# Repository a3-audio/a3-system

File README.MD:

# Ambijocky

Goal for this project is a Hardware Controller which enables everybody, who can use a dj-mixer, to perform
LIVE on a 3d-Audio-sphere (Ambisonic). You should consider it as loopmachine for panning motions. It
includes audiostream analysis to create a reliable live beatclock, wich let the user control step motions
out of bars, steps and bpm).

It consists of three elements:

- The Server which runs the audio and osc-routing-engine (live io-processing)
- The Mixercontroller: it looks like a 4-channel dj-mixer but just handles osc
- The Motioncontroller: the touchscreen records and shows actual position and width for all 4 stereo
  channels at the same time. Also it has 4 store/recall buttons and some potis/encoders for motionmodes
  and sequence parameters.

## Blackboard

### TODO`s

- beat-counter / beat-detection
- OSC looper
- Motion-contoler
  - GUI
    - Motion-inticator für jeden kana erstellen
    - farbe
    - OSC-adressen eintragen
  - documentieren

### Hardware

Die Stecker die wie fur die Portis etc. wollen sind **JST XH 2.54mm**

- [WS2811 NeoPixel LED Driver Chip](https://www.adafruit.com/product/1378)
- [NeoPixel 5mm Through-Hole LED](https://www.adafruit.com/product/1938)
- [OLED Butten](https://www.alibaba.com/product-detail/Lakeview-DSP-OLED-LCD-Display-Screen_60759925392.html?spm=a2700.details.deiletai6.3.74dd7a76xJLr4l)
- [RGB Button](https://www.alibaba.com/product-detail/Lakeview-RGB-Full-Color-Momentary-Illuminated_60769825493.html?bypass=true)
- [RGB Tactile Button](https://www.alibaba.com/product-detail/Lakeview-TL3-RGB-Momentary-LED-Super_60769192488.html?spm=a2700.details.deiletai6.6.5a067a76Q1eRKz&bypass=true)

## dependencies

- Python3
- platformio
- [Reaper](https://www.reaper.fm/)
- [IEM Plug-in Suite](https://plugins.iem.at/)

## code of conduct

1. Don't panic

2. care the docs

3. keep the Code clean

4. Hinterlasse nichts, auser deiner Wurst.

5. Easter Eggs are welcome!

### git

To be simple we decided to use centralized workflow, described here:
https://www.git-scm.com/book/en/v2/Distributed-Git-Distributed-Workflows

1. Der Main Branch darf nicht direkt bearbeitet werden, die edits sollten immer in einem seperarten Branch gemacht werden und dann über ein pull requests zusammen gefügt werden. Die Ausnahmen bilden das [Balckboard](#Balckboard) in deiser README und die korektur von offensichtlichen Rechtschreibfehlern in der Doku.

2. wenn du dir ein eigenes Setup bauen willst, erstelle dir ein Forg, um es an dich anzupassen

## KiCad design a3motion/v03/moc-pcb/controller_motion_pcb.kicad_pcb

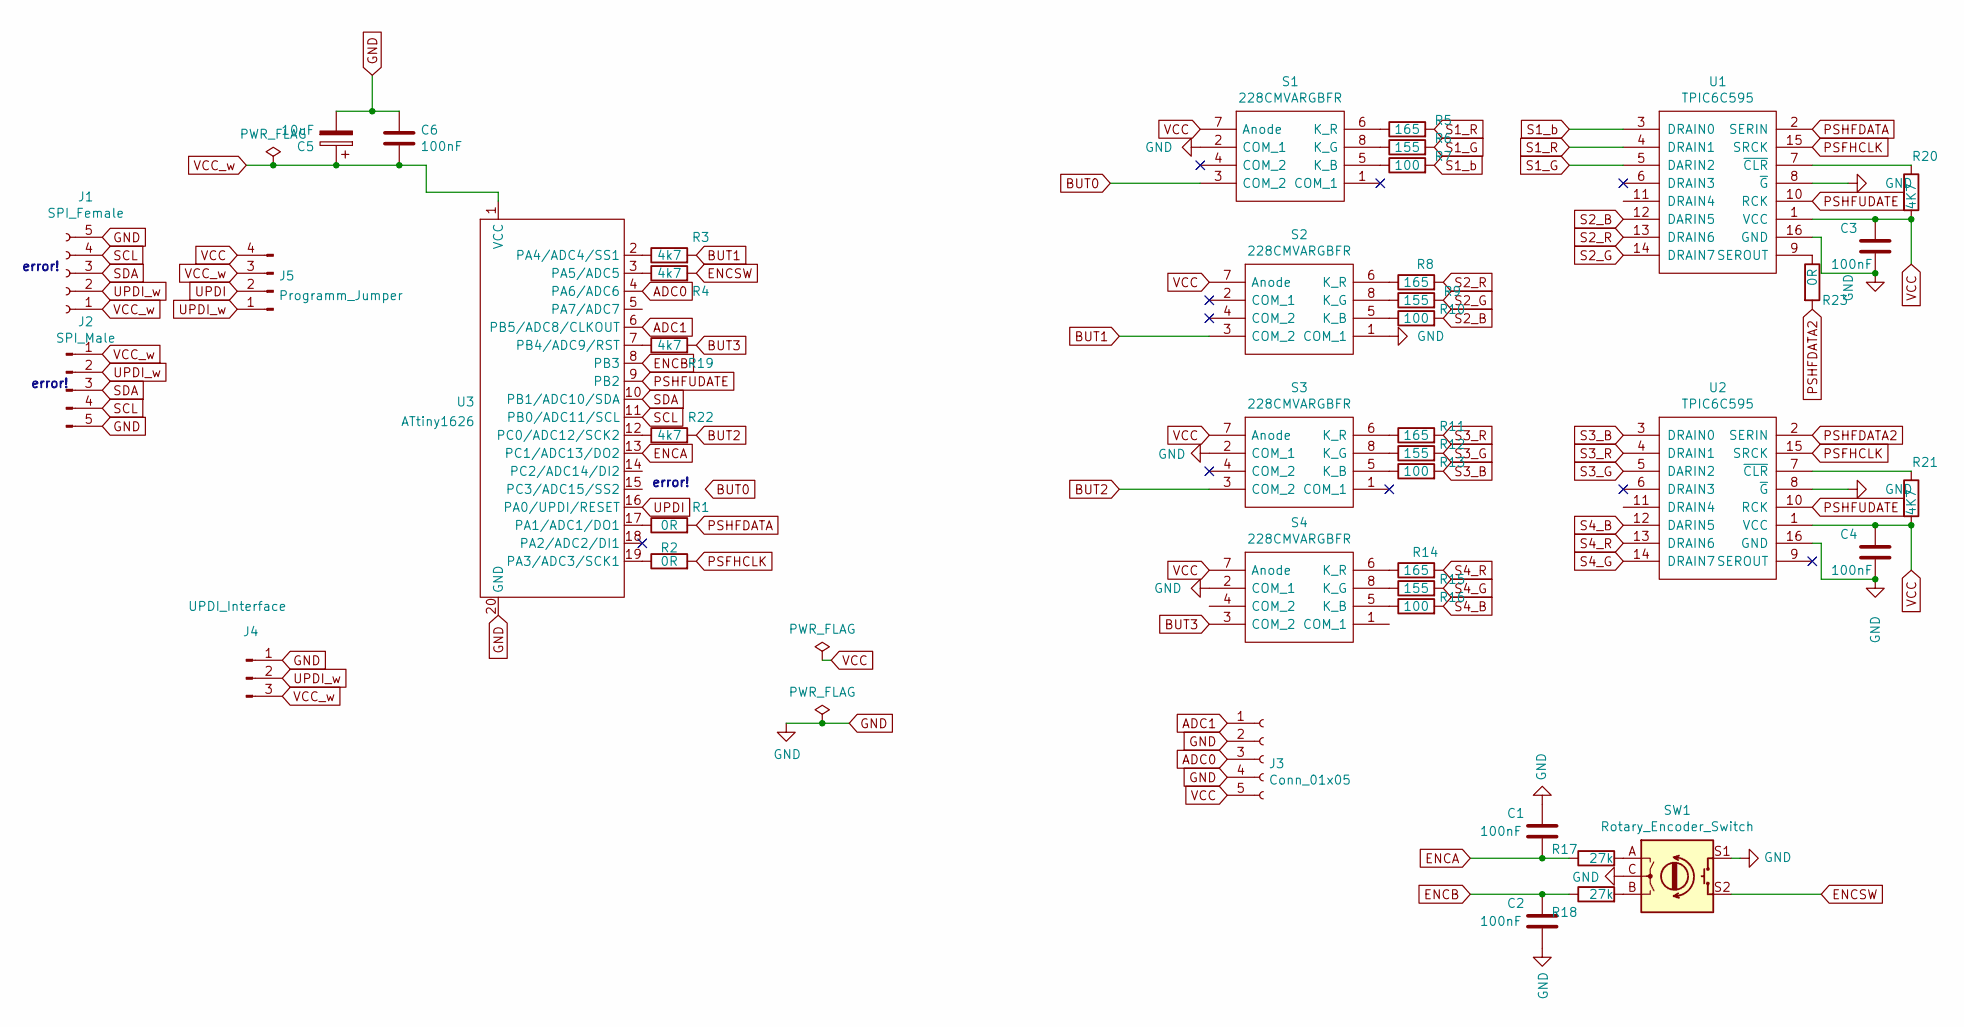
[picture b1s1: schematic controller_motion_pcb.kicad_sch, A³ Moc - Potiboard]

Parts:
C1, C2, C3, C4, C6: 100nF; C_1206_3216Metric_Pad1.33x1.80mm_HandSolder
C5: 10uF; CP_Radial_D4.0mm_P1.50mm
J1: SPI_Female; PinSocket_1x05_P2.54mm_Horizontal
J2: SPI_Male; PinHeader_1x05_P2.54mm_Horizontal
J3: Conn_01x05; JST_XH_B5B-XH-A_1x05_P2.50mm_Vertical
J4: UPDI_Interface; PinHeader_1x03_P2.54mm_Vertical
J5: Programm_Jumper; PinHeader_2x02_P2.54mm_Vertical
R1, R2, R23: 0R; R_1206_3216Metric_Pad1.30x1.75mm_HandSolder
R3, R4, R19, R22: 4k7; R_1206_3216Metric_Pad1.30x1.75mm_HandSolder
R5, R8, R11, R14: 165; R_1206_3216Metric_Pad1.30x1.75mm_HandSolder
R6, R9, R12, R15: 155; R_1206_3216Metric_Pad1.30x1.75mm_HandSolder
R7, R10, R13, R16: 100; R_1206_3216Metric_Pad1.30x1.75mm_HandSolder
R17, R18: 27k; R_1206_3216Metric_Pad1.30x1.75mm_HandSolder
R20, R21: 4K7; R_1206_3216Metric_Pad1.30x1.75mm_HandSolder
S1, S2, S3, S4: 228CMVARGBFR; 228CMVARGBFR_SMD; Mouser Part Number 774-228CMVARGBFR
SW1: Rotary_Encoder_Switch; PEC11R4230KS0024
U1, U2: TPIC6C595; SOIC-16_3.9x9.9mm_P1.27mm
U3: ATtiny1626; attiny1626

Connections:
ADC0: J3.3, U3.4 (PA6/ADC6)
BUT0: S1.3 (COM_2)
BUT1: R3.2, S2.3 (COM_2)
BUT2: R22.2, S3.3 (COM_2)
BUT3: R19.2, S4.3 (COM_2)
ENCA: C1.2, R17.1, U3.13 (PC1/ADC13/DO2)
ENCB: C2.1, R18.1, U3.8 (PB3)
ENCSW: R4.2, SW1.S2
GND: C1.1, C2.2, C3.2, C4.2, C5.2, C6.1, J1.5, J2.5, J3.2, J3.4, J4.1, S1.2 (COM_1), S2.1 (COM_1), S3.2 (COM_1), S4.2 (COM_1), SW1.C, SW1.S1, U1.8 (~G), U1.16 (GND), U2.8 (~G), U2.16 (GND), U3.20 (GND)
unnamed: R1.1, U3.17 (PA1/ADC1/DO1)
unnamed: R2.1, U3.19 (PA3/ADC3/SCK1)
unnamed: R3.1, U3.2 (PA4/ADC4/SS1)
unnamed: R4.1, U3.3 (PA5/ADC5)
unnamed: R5.1, S1.6 (K_R)
unnamed: R6.1, S1.8 (K_G)
unnamed: R7.1, S1.5 (K_B)
unnamed: R8.1, S2.6 (K_R)
unnamed: R9.1, S2.8 (K_G)
unnamed: R10.1, S2.5 (K_B)
unnamed: R11.1, S3.6 (K_R)
unnamed: R12.1, S3.8 (K_G)
unnamed: R13.1, S3.5 (K_B)
unnamed: R14.1, S4.6 (K_R)
unnamed: R15.1, S4.8 (K_G)
unnamed: R16.1, S4.5 (K_B)
unnamed: R17.2, SW1.A
unnamed: R18.2, SW1.B
unnamed: R19.1, U3.7 (PB4/ADC9/RST)
unnamed: R20.1, U1.7 (~CLR)
unnamed: R21.1, U2.7 (~CLR)
unnamed: R22.1, U3.12 (PC0/ADC12/SCK2)
unnamed: R23.1, U1.9 (SEROUT)
PSFHCLK: R2.2, U1.15 (SRCK), U2.15 (SRCK)
PSHFDATA: R1.2, U1.2 (SERIN)
PSHFDATA2: R23.2, U2.2 (SERIN)
PSHFUDATE: U1.10 (RCK), U2.10 (RCK), U3.9 (PB2)
S1_G: R6.2, U1.5 (DARIN2)
S1_R: R5.2, U1.4 (DRAIN1)
S1_b: R7.2, U1.3 (DRAIN0)
S2_B: R10.2, U1.12 (DARIN5)
S2_G: R9.2, U1.14 (DRAIN7)
S2_R: R8.2, U1.13 (DRAIN6)
S3_B: R13.2, U2.3 (DRAIN0)
S3_G: R12.2, U2.5 (DARIN2)
S3_R: R11.2, U2.4 (DRAIN1)
S4_B: R16.2, U2.12 (DARIN5)
S4_G: R15.2, U2.14 (DRAIN7)
S4_R: R14.2, U2.13 (DRAIN6)
SCL: J1.4, J2.4, U3.11 (PB0/ADC11/SCL)
SDA: J1.3, J2.3, U3.10 (PB1/ADC10/SDA)
UPDI: J5.2, U3.16 (PA0/UPDI/RESET)
UPDI_w: J1.2, J2.2, J4.2, J5.1
VCC_w: C5.1, C6.2, J1.1, J2.1, J4.3, J5.3, U3.1 (VCC)

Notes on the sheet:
error!

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
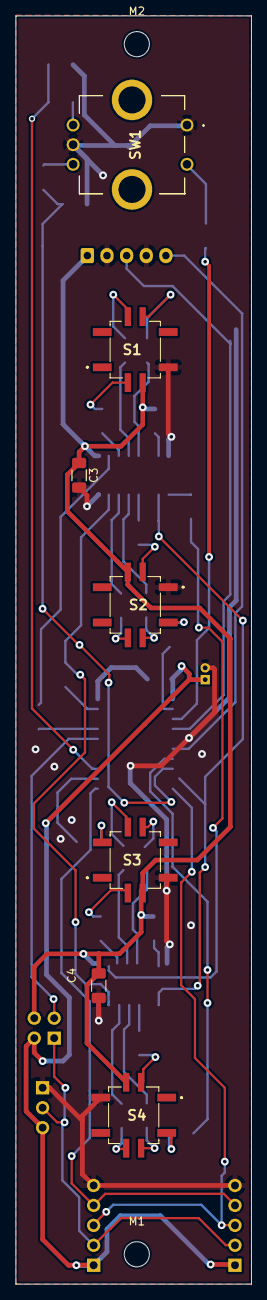
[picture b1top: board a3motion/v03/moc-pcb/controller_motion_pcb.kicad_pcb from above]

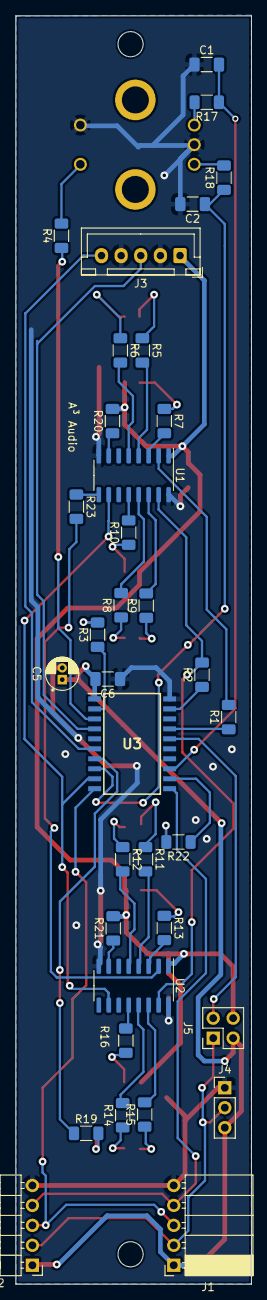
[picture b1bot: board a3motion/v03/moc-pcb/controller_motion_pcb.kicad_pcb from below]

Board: 2 copper layers, 30.0 x 161.5 mm, 44 parts (35 on the bottom side), 54 nets.

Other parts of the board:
M1, M2: MountingHole_3.2mm_M3

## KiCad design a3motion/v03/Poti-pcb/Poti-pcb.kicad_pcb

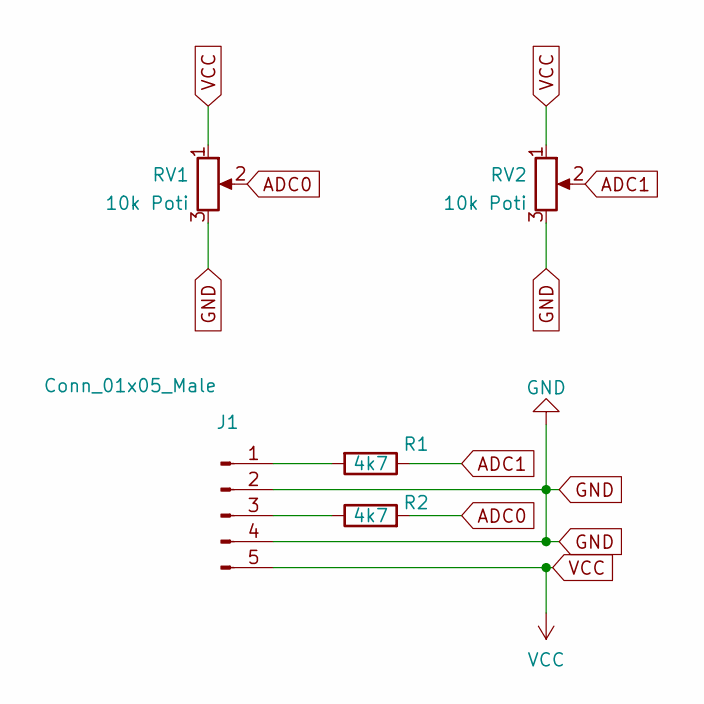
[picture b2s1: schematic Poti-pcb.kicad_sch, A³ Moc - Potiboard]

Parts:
J1: Conn_01x05_Male; JST_XH_B5B-XH-A_1x05_P2.50mm_Vertical
R1, R2: 4k7; R_1206_3216Metric_Pad1.30x1.75mm_HandSolder
RV1, RV2: 10k Poti; Potentiometer_Alpha_RD901F-40-00D_Single_Vertical_CircularH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

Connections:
ADC0: R2.2, RV1.2
ADC1: R1.1, RV2.2
GND: J1.2, J1.4, RV1.3, RV2.3
unnamed: J1.1, R1.2
unnamed: J1.3, R2.1
VCC: J1.5, RV1.1, RV2.1

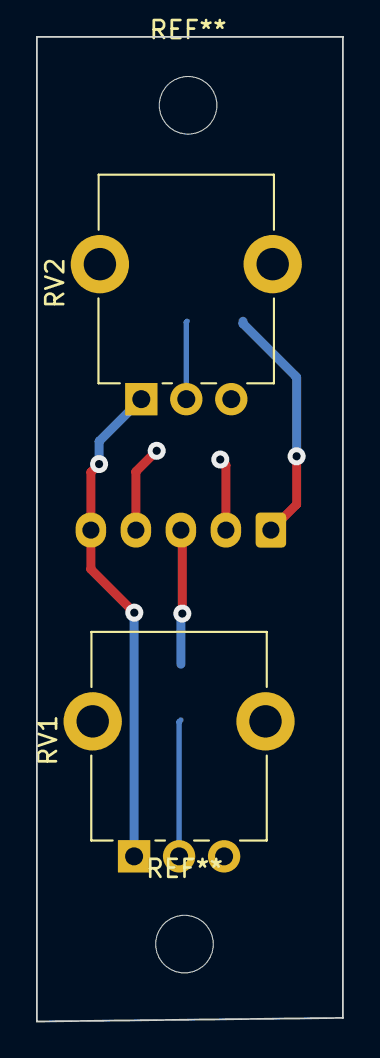
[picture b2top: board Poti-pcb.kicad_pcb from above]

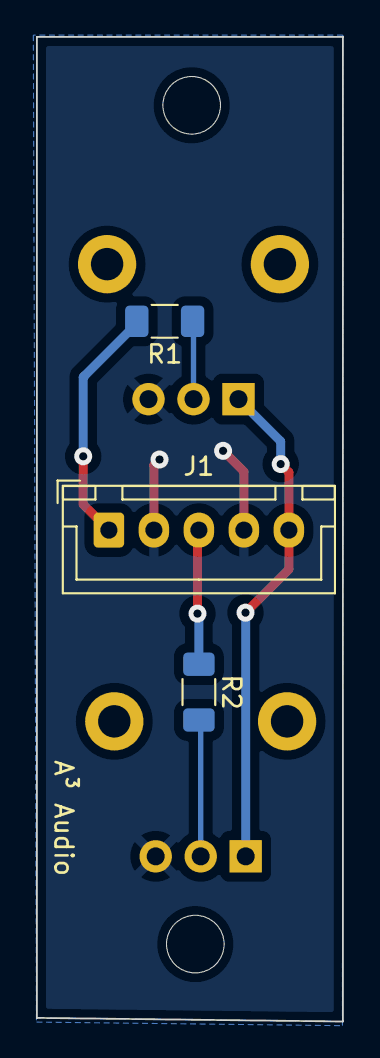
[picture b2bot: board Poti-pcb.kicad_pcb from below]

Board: 2 copper layers, 17.0 x 54.7 mm, 5 parts (3 on the bottom side), 6 nets.

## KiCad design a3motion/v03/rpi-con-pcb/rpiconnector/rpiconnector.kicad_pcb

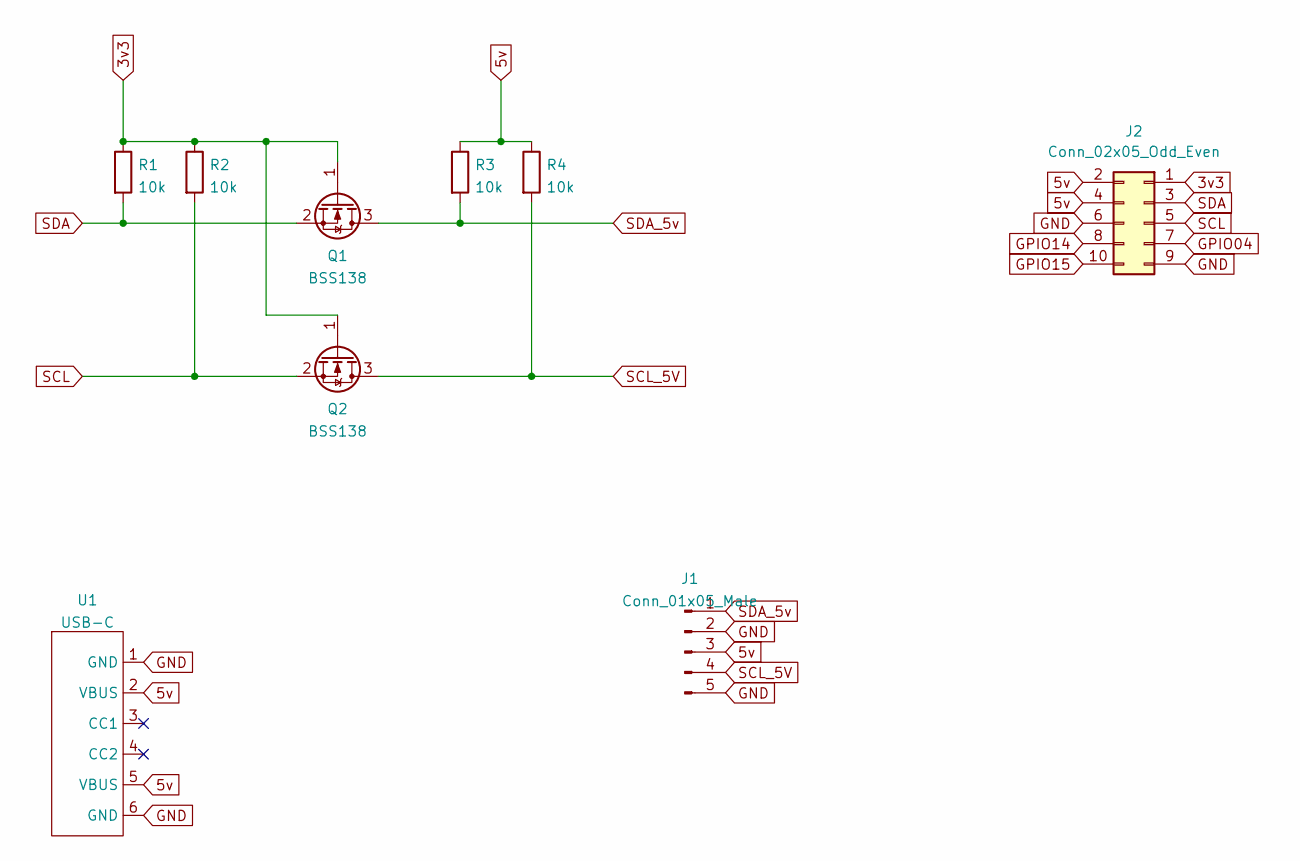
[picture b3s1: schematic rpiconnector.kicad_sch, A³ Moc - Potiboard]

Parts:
J1: Conn_01x05_Male; PinHeader_1x05_P2.54mm_Vertical
J2: Conn_02x05_Odd_Even; PinSocket_2x05_P2.54mm_Vertical
Q1, Q2: BSS138
R1, R2, R3, R4: 10k; R_1206_3216Metric_Pad1.30x1.75mm_HandSolder
U1: USB-C

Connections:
3v3: J2.1, Q1.1 (G), Q2.1 (G), R1.1, R2.1
5v: J1.3, J2.2, J2.4, R3.1, R4.1, U1.2 (VBUS), U1.5 (VBUS)
GND: J1.2, J1.5, J2.6, J2.9, U1.1 (GND), U1.6 (GND)
GPIO04: J2.7
GPIO14: J2.8
GPIO15: J2.10
SCL: J2.5, Q2.2 (S), R2.2
SCL_5V: J1.4, Q2.3 (D), R4.2
SDA: J2.3, Q1.2 (S), R1.2
SDA_5v: J1.1, Q1.3 (D), R3.2

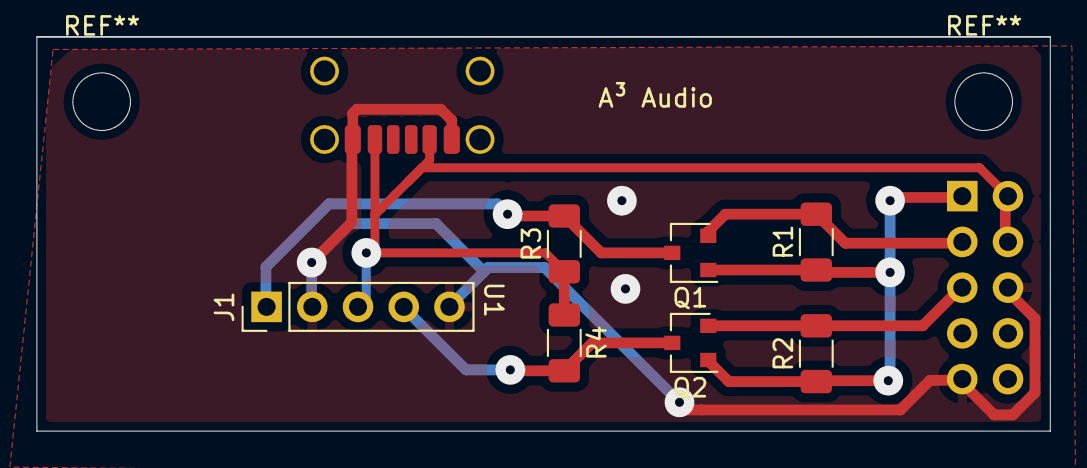
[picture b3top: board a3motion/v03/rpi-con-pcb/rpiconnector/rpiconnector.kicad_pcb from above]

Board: 2 copper layers, 56.3 x 21.9 mm, 9 parts (1 on the bottom side), 7 nets.

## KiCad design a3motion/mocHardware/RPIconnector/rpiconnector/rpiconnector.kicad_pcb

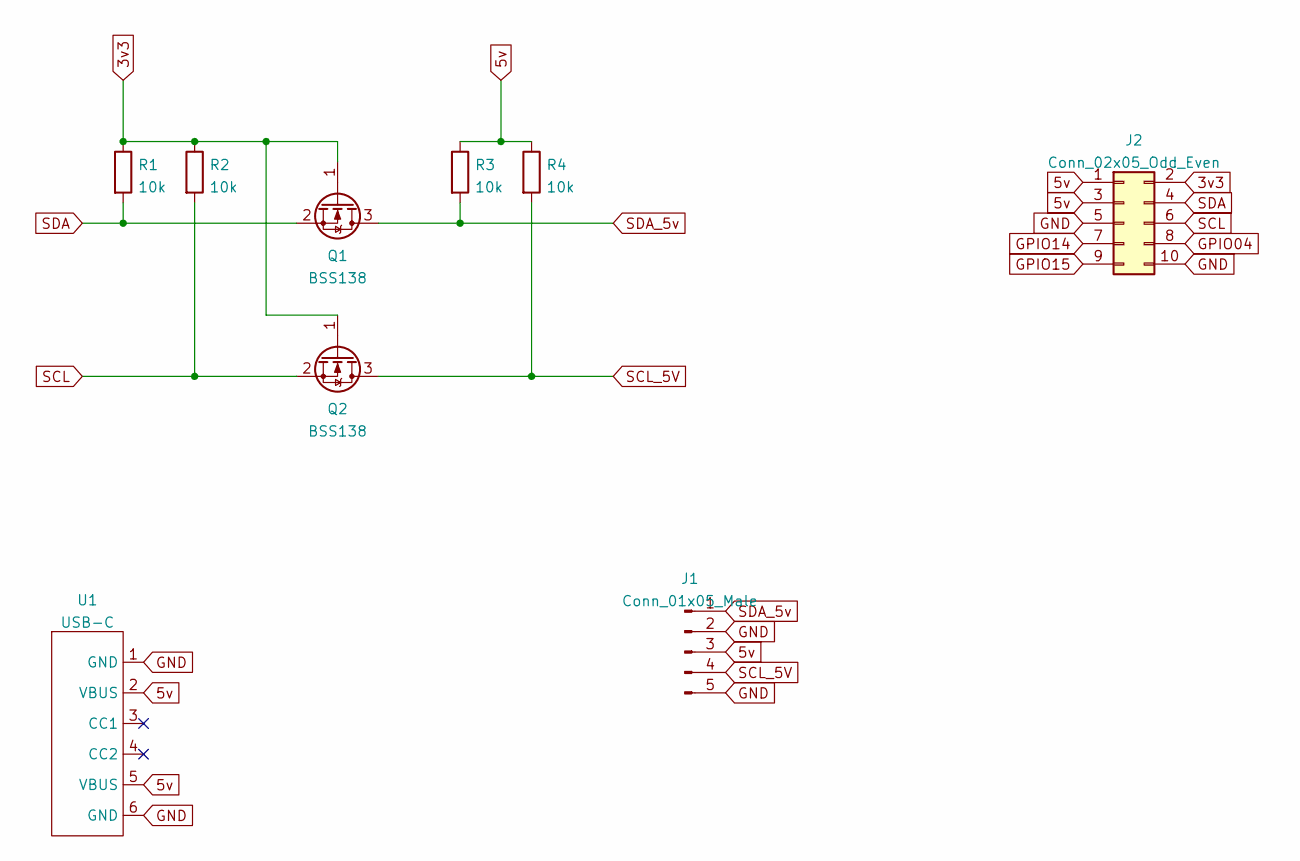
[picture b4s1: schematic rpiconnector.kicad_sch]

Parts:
J1: Conn_01x05_Male; PinHeader_1x05_P2.54mm_Vertical
J2: Conn_02x05_Odd_Even; PinHeader_2x05_P2.54mm_Vertical
Q1, Q2: BSS138; SOT-23
R1, R2, R3, R4: 10k; R_1206_3216Metric_Pad1.30x1.75mm_HandSolder
U1: USB-C

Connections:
3v3: J2.2, Q1.1 (G), Q2.1 (G), R1.1, R2.1
5v: J1.3, J2.1, J2.3, R3.1, R4.1, U1.2 (VBUS), U1.5 (VBUS)
GND: J1.2, J1.5, J2.5, J2.10, U1.1 (GND), U1.6 (GND)
GPIO04: J2.8
GPIO14: J2.7
GPIO15: J2.9
SCL: J2.6, Q2.2 (S), R2.2
SCL_5V: J1.4, Q2.3 (D), R4.2
SDA: J2.4, Q1.2 (S), R1.2
SDA_5v: J1.1, Q1.3 (D), R3.2

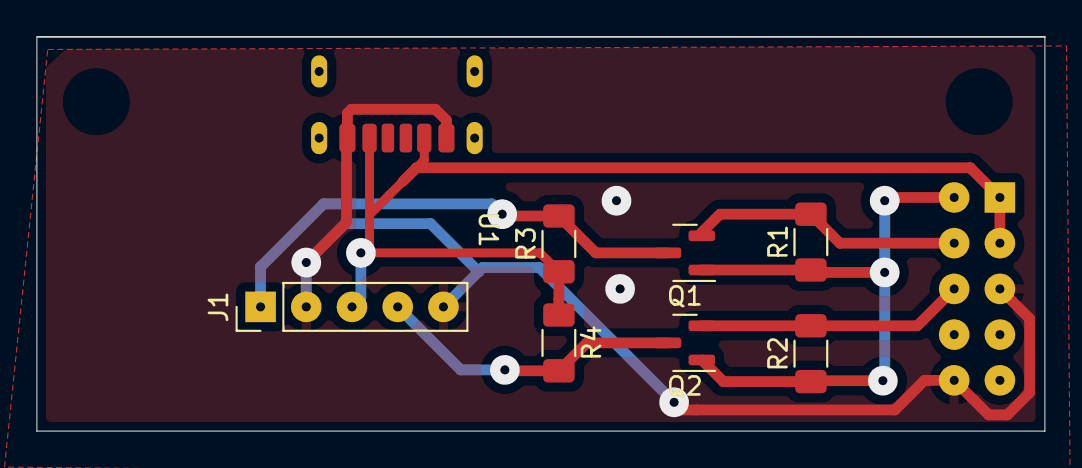
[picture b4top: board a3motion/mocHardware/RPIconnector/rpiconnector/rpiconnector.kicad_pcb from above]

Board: 2 copper layers, 56.0 x 21.9 mm, 9 parts (1 on the bottom side), 7 nets.

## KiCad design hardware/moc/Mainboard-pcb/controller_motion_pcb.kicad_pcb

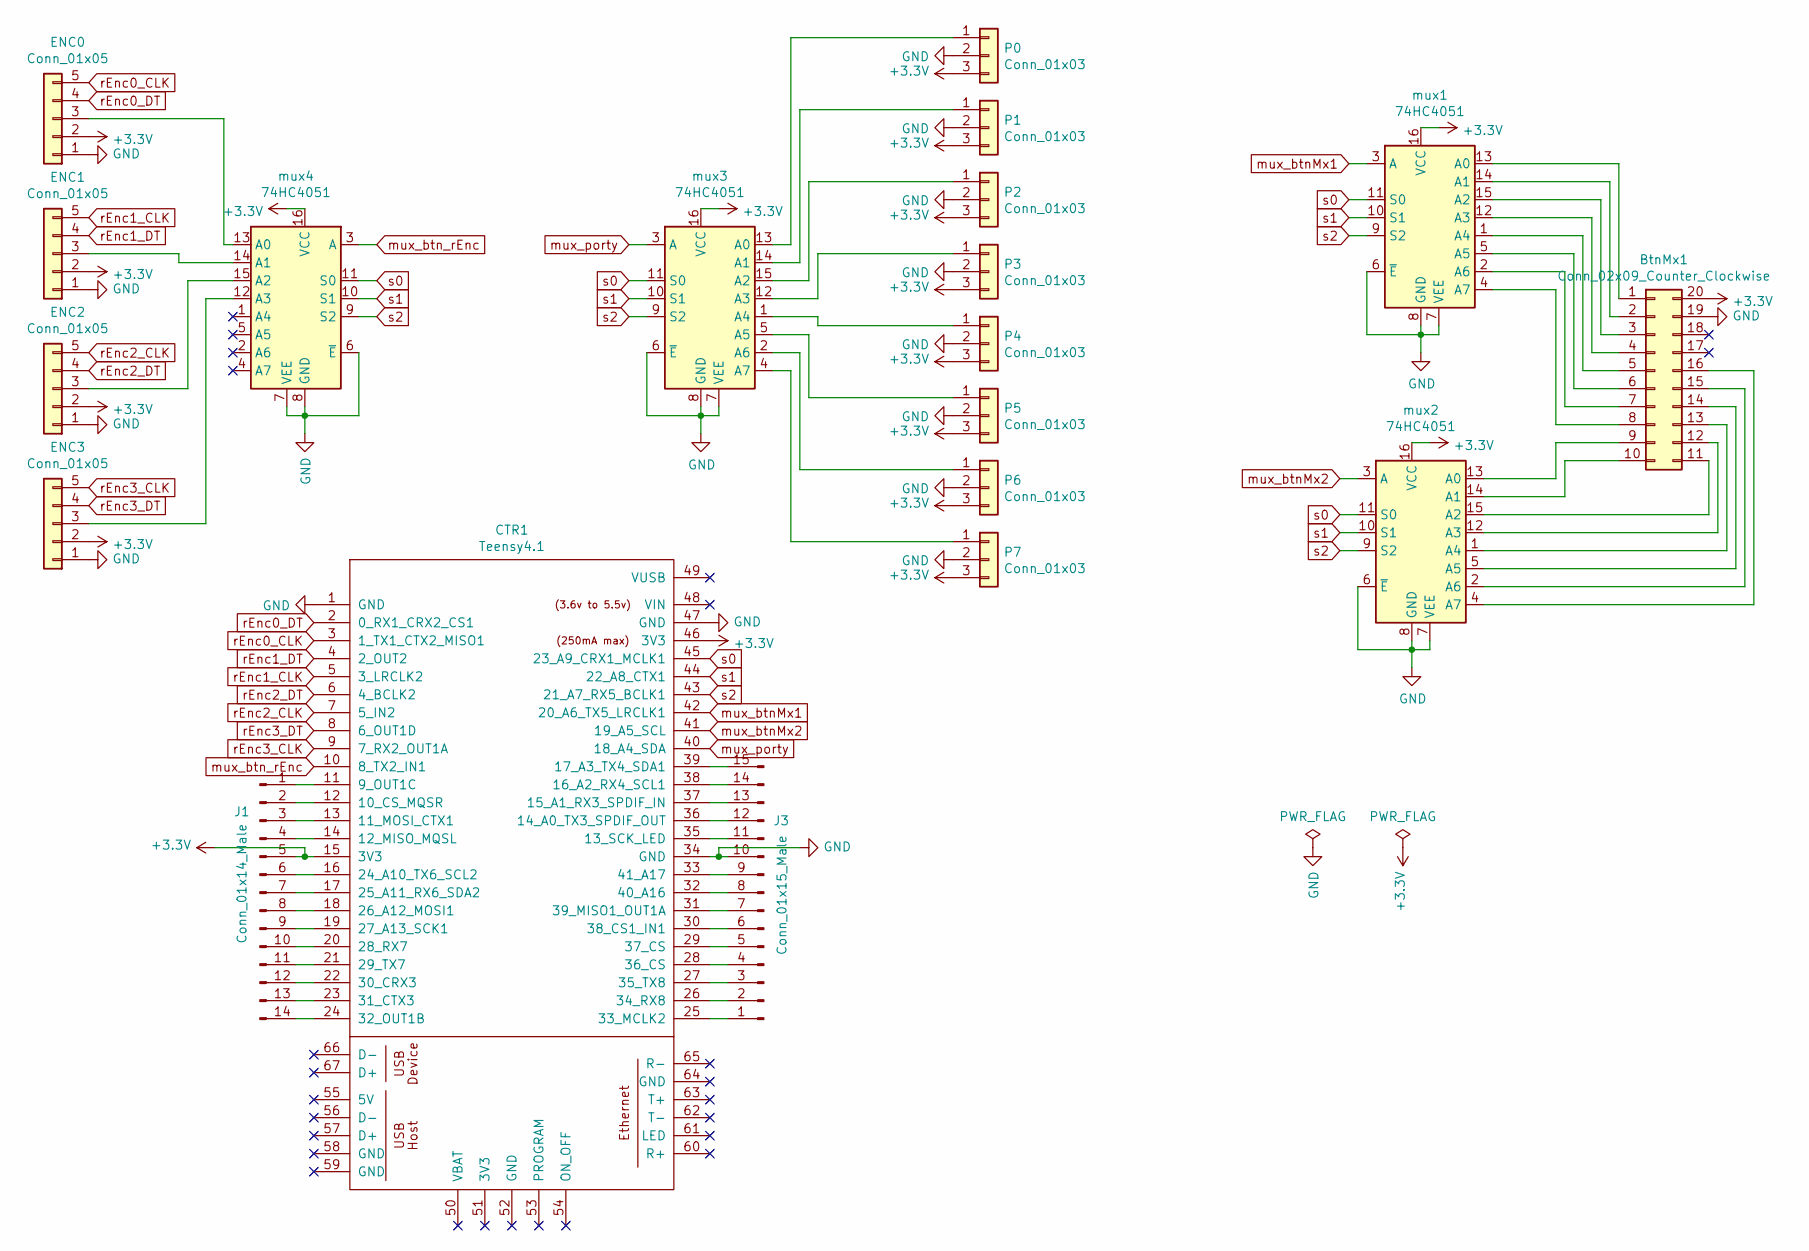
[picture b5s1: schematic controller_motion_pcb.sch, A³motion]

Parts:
BtnMx1: Conn_02x09_Counter_Clockwise; IDC-Header_2x10_P2.54mm_Vertical
CTR1: Teensy4.1; Teensy41
ENC0, ENC1, ENC2, ENC3: Conn_01x05; JST_EH_B5B-EH-A_1x05_P2.50mm_Vertical
J1: Conn_01x14_Male; PinHeader_1x14_P2.54mm_Vertical
J3: Conn_01x15_Male; PinHeader_1x15_P2.54mm_Vertical
P0, P1, P2, P3, P4, P5, P6, P7: Conn_01x03; JST_EH_B3B-EH-A_1x03_P2.50mm_Vertical
mux1, mux2, mux3, mux4: 74HC4051; DIP-16_W7.62mm

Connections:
+3V3: BtnMx1.20, CTR1.15 (3V3), CTR1.46 (3V3), ENC0.2, ENC1.2, ENC2.2, ENC3.2, J1.5, P0.3, P1.3, P2.3, P3.3, P4.3, P5.3, P6.3, P7.3, mux1.16 (VCC), mux2.16 (VCC), mux3.16 (VCC), mux4.16 (VCC)
GND: BtnMx1.19, CTR1.1 (GND), CTR1.34 (GND), CTR1.47 (GND), ENC0.1, ENC1.1, ENC2.1, ENC3.1, J3.10, P0.2, P1.2, P2.2, P3.2, P4.2, P5.2, P6.2, P7.2, mux1.6 (~E), mux1.7 (VEE), mux1.8 (GND), mux2.6 (~E), mux2.7 (VEE), mux2.8 (GND), mux3.6 (~E), mux3.7 (VEE), mux3.8 (GND), mux4.6 (~E), mux4.7 (VEE), mux4.8 (GND)
unnamed: BtnMx1.1, mux1.13 (A0)
unnamed: BtnMx1.2, mux1.14 (A1)
unnamed: BtnMx1.3, mux1.15 (A2)
unnamed: BtnMx1.4, mux1.12 (A3)
unnamed: BtnMx1.5, mux1.1 (A4)
unnamed: BtnMx1.6, mux1.5 (A5)
unnamed: BtnMx1.7, mux1.2 (A6)
unnamed: BtnMx1.8, mux1.4 (A7)
unnamed: BtnMx1.9, mux2.13 (A0)
unnamed: BtnMx1.10, mux2.14 (A1)
unnamed: BtnMx1.11, mux2.15 (A2)
unnamed: BtnMx1.12, mux2.12 (A3)
unnamed: BtnMx1.13, mux2.1 (A4)
unnamed: BtnMx1.14, mux2.5 (A5)
unnamed: BtnMx1.15, mux2.2 (A6)
unnamed: BtnMx1.16, mux2.4 (A7)
unnamed: CTR1.11 (9_OUT1C), J1.1
unnamed: CTR1.12 (10_CS_MQSR), J1.2
unnamed: CTR1.13 (11_MOSI_CTX1), J1.3
unnamed: CTR1.14 (12_MISO_MQSL), J1.4
unnamed: CTR1.16 (24_A10_TX6_SCL2), J1.6
unnamed: CTR1.17 (25_A11_RX6_SDA2), J1.7
unnamed: CTR1.18 (26_A12_MOSI1), J1.8
unnamed: CTR1.19 (27_A13_SCK1), J1.9
unnamed: CTR1.20 (28_RX7), J1.10
unnamed: CTR1.21 (29_TX7), J1.11
unnamed: CTR1.22 (30_CRX3), J1.12
unnamed: CTR1.23 (31_CTX3), J1.13
unnamed: CTR1.24 (32_OUT1B), J1.14
unnamed: CTR1.25 (33_MCLK2), J3.1
unnamed: CTR1.26 (34_RX8), J3.2
unnamed: CTR1.27 (35_TX8), J3.3
unnamed: CTR1.28 (36_CS), J3.4
unnamed: CTR1.29 (37_CS), J3.5
unnamed: CTR1.30 (38_CS1_IN1), J3.6
unnamed: CTR1.31 (39_MISO1_OUT1A), J3.7
unnamed: CTR1.32 (40_A16), J3.8
unnamed: CTR1.33 (41_A17), J3.9
unnamed: CTR1.35 (13_SCK_LED), J3.11
unnamed: CTR1.36 (14_A0_TX3_SPDIF_OUT), J3.12
unnamed: CTR1.37 (15_A1_RX3_SPDIF_IN), J3.13
unnamed: CTR1.38 (16_A2_RX4_SCL1), J3.14
unnamed: CTR1.39 (17_A3_TX4_SDA1), J3.15
unnamed: ENC0.3, mux4.13 (A0)
unnamed: ENC1.3, mux4.14 (A1)
unnamed: ENC2.3, mux4.15 (A2)
unnamed: ENC3.3, mux4.12 (A3)
unnamed: P0.1, mux3.13 (A0)
unnamed: P1.1, mux3.14 (A1)
unnamed: P2.1, mux3.15 (A2)
unnamed: P3.1, mux3.12 (A3)
unnamed: P4.1, mux3.1 (A4)
unnamed: P5.1, mux3.5 (A5)
unnamed: P6.1, mux3.2 (A6)
unnamed: P7.1, mux3.4 (A7)
mux_btnMx1: CTR1.42 (20_A6_TX5_LRCLK1), mux1.3 (A)
mux_btnMx2: CTR1.41 (19_A5_SCL), mux2.3 (A)
mux_btn_rEnc: CTR1.10 (8_TX2_IN1), mux4.3 (A)
mux_porty: CTR1.40 (18_A4_SDA), mux3.3 (A)
rEnc0_CLK: CTR1.3 (1_TX1_CTX2_MISO1), ENC0.5
rEnc0_DT: CTR1.2 (0_RX1_CRX2_CS1), ENC0.4
rEnc1_CLK: CTR1.5 (3_LRCLK2), ENC1.5
rEnc1_DT: CTR1.4 (2_OUT2), ENC1.4
rEnc2_CLK: CTR1.7 (5_IN2), ENC2.5
rEnc2_DT: CTR1.6 (4_BCLK2), ENC2.4
rEnc3_CLK: CTR1.9 (7_RX2_OUT1A), ENC3.5
rEnc3_DT: CTR1.8 (6_OUT1D), ENC3.4
s0: CTR1.45 (23_A9_CRX1_MCLK1), mux1.11 (S0), mux2.11 (S0), mux3.11 (S0), mux4.11 (S0)
s1: CTR1.44 (22_A8_CTX1), mux1.10 (S1), mux2.10 (S1), mux3.10 (S1), mux4.10 (S1)
s2: CTR1.43 (21_A7_RX5_BCLK1), mux1.9 (S2), mux2.9 (S2), mux3.9 (S2), mux4.9 (S2)

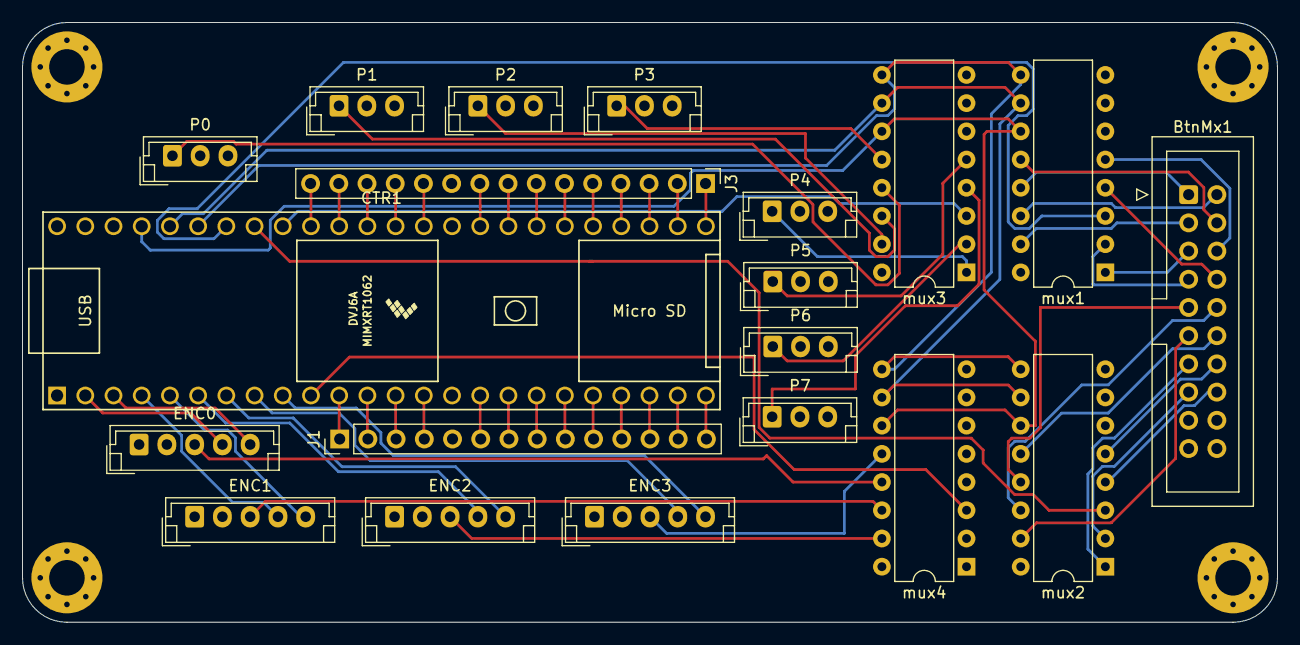
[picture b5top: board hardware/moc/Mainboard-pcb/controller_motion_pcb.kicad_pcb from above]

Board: 4 copper layers, 113.0 x 54.0 mm, 20 parts (0 on the bottom side), 72 nets.

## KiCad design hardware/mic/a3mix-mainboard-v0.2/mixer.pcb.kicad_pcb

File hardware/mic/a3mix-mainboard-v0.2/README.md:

This Project comes with its own libraries.

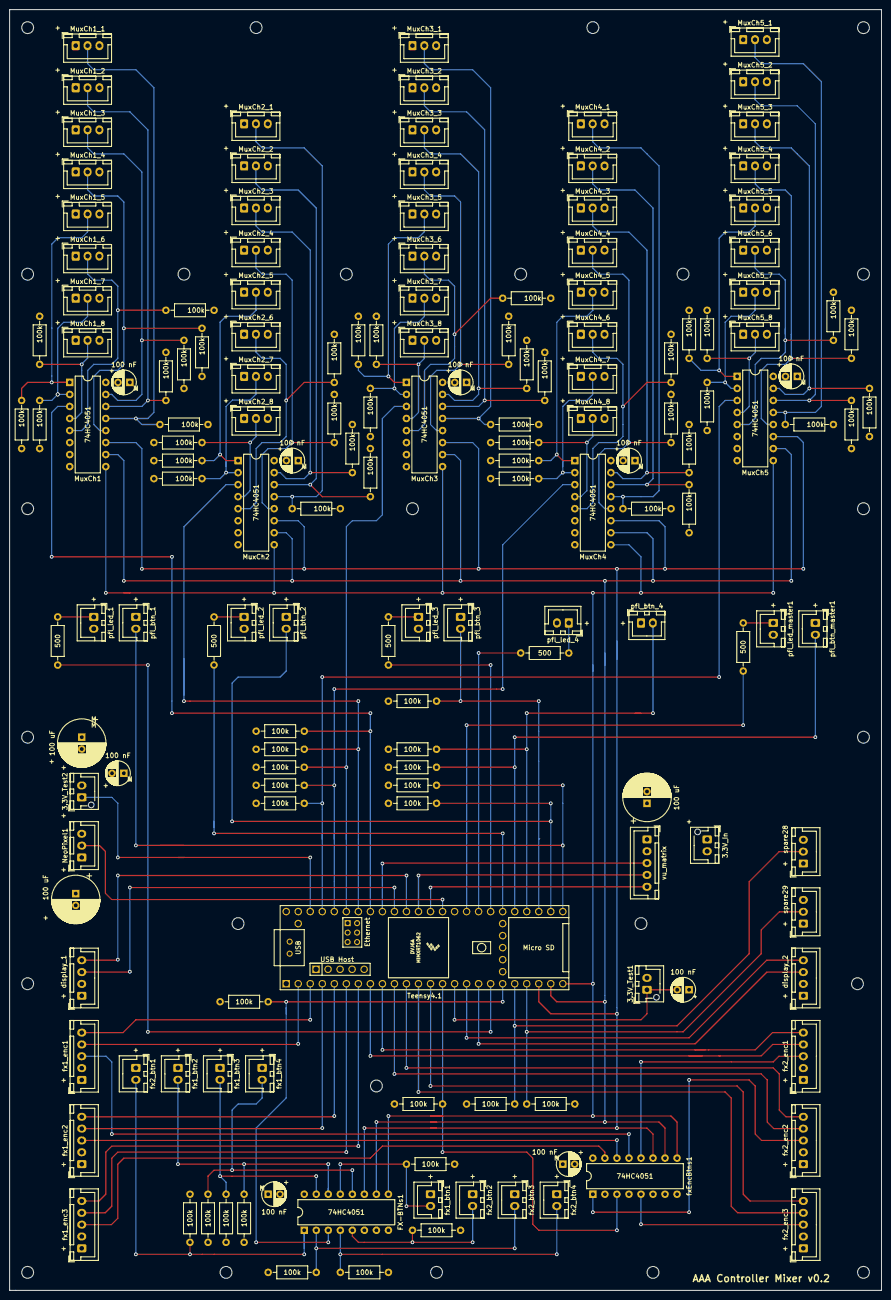
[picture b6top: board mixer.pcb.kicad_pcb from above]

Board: 4 copper layers, 184.2 x 270.5 mm, 160 parts (0 on the bottom side), 105 nets.

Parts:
3.3V_In, 3.3V_Test1, 3.3V_Test2: Conn_01x02; JST_XH_B2B-XH-AM_1x02_P2.50mm_Vertical
C1, C2, C7: 100 uF; CP_Radial_D10.0mm_P2.50mm
C3, C4, C5, C6, C8, C9, C10, C11, C12: 100 nF; CP_Radial_D5.0mm_P2.50mm
FX-BTNs1: 74HC4051; DIP-16_W7.62mm
MuxCh1, MuxCh2, MuxCh3, MuxCh4, MuxCh5: 74HC4051; DIP-16_W7.62mm
MuxCh1_1, MuxCh1_2, MuxCh1_3, MuxCh1_4, MuxCh1_5, MuxCh1_6, MuxCh1_7, MuxCh1_8, MuxCh2_1, MuxCh2_2, MuxCh2_3, MuxCh2_4, MuxCh2_5, MuxCh2_6, MuxCh2_7, MuxCh2_8, MuxCh3_1, MuxCh3_2, MuxCh3_3, MuxCh3_4, MuxCh3_5, MuxCh3_6, MuxCh3_7, MuxCh3_8, MuxCh4_1, MuxCh4_2, MuxCh4_3, MuxCh4_4, MuxCh4_5, MuxCh4_6, MuxCh4_7, MuxCh4_8, MuxCh5_1, MuxCh5_2, MuxCh5_3, MuxCh5_4, MuxCh5_5, MuxCh5_6, MuxCh5_7, MuxCh5_8: Conn_01x03; JST_XH_B3B-XH-A_1x03_P2.50mm_Vertical
NeoPixel1: Conn_01x03; JST_XH_B3B-XH-A_1x03_P2.50mm_Vertical
R1, R2, R3, R4, R5, R6, R7, R8, R9, R10, R11, R12, R13, R14, R15, R16, R17, R19, R20, R21, R22, R23, R24, R25, R26, R27, R28, R29, R34, R35, R36, R37, R38, R39, R40, R41, R42, R43, R44, R45, R46, R47, R48, R49, R50, R51, R52, R53, R54, R55, R56, R57, R58, R59, R60, R61, R62, R63, R64, R65, R66, R67: 100k; R_Axial_DIN0207_L6.3mm_D2.5mm_P10.16mm_Horizontal
R18, R30, R31, R32, R33: 500; R_Axial_DIN0207_L6.3mm_D2.5mm_P10.16mm_Horizontal
U5: Teensy4.1; Teensy41
display_1, display_2: Conn_01x04; JST_XH_B4B-XH-A_1x04_P2.50mm_Vertical
fx1_btn1, fx1_btn2, fx1_btn3, fx1_btn4, fx2_btn1, fx2_btn2, fx2_btn3, fx2_btn4: Conn_01x02; JST_XH_B2B-XH-A_1x02_P2.50mm_Vertical
fx1_enc1, fx1_enc2, fx1_enc3, fx2_enc1, fx2_enc2, fx2_enc3: Conn_01x05; JST_XH_B5B-XH-A_1x05_P2.50mm_Vertical
fxEncBtns1: 74HC4051; DIP-16_W7.62mm
pfl_btn_1, pfl_btn_2, pfl_btn_3, pfl_btn_4: Conn_01x02; JST_XH_B2B-XH-A_1x02_P2.50mm_Vertical
pfl_btn_master1: Conn_01x02; JST_XH_B2B-XH-A_1x02_P2.50mm_Vertical
pfl_led_1, pfl_led_2, pfl_led_3, pfl_led_4: Conn_01x02; JST_XH_B2B-XH-A_1x02_P2.50mm_Vertical
pfl_led_master1: Conn_01x02; JST_XH_B2B-XH-A_1x02_P2.50mm_Vertical
spare28, spare29: Conn_01x03; JST_XH_B3B-XH-A_1x03_P2.50mm_Vertical
vu_matrix: MAX7219 led matrix vu; JST_XH_B5B-XH-A_1x05_P2.50mm_Vertical

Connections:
+3V3: 3.3V_In.1, 3.3V_Test1.2, 3.3V_Test2.2, C1.1, C2.1, C4.2, C5.2, C6.2, C7.2, C8.2, C9.2, C10.2, C11.2, C12.2, FX-BTNs1.16, MuxCh1.16, MuxCh1_1.1, MuxCh1_2.1, MuxCh1_3.1, MuxCh1_4.1, MuxCh1_5.1, MuxCh1_6.1, MuxCh1_7.1, MuxCh1_8.1, MuxCh2.16, MuxCh2_1.1, MuxCh2_2.1, MuxCh2_3.1, MuxCh2_4.1, MuxCh2_5.1, MuxCh2_6.1, MuxCh2_7.1, MuxCh2_8.1, MuxCh3.16, MuxCh3_1.1, MuxCh3_2.1, MuxCh3_3.1, MuxCh3_4.1, MuxCh3_5.1, MuxCh3_6.1, MuxCh3_7.1, MuxCh3_8.1, MuxCh4.16, MuxCh4_1.1, MuxCh4_2.1, MuxCh4_3.1, MuxCh4_4.1, MuxCh4_5.1, MuxCh4_6.1, MuxCh4_7.1, MuxCh4_8.1, MuxCh5.16, MuxCh5_1.1, MuxCh5_2.1, MuxCh5_3.1, MuxCh5_4.1, MuxCh5_5.1, MuxCh5_6.1, MuxCh5_7.1, MuxCh5_8.1, NeoPixel1.1, display_1.1, display_2.1, fx1_btn1.1, fx1_btn2.1, fx1_btn3.1, fx1_btn4.1, fx1_enc1.1, fx1_enc2.1, fx1_enc3.1, fx2_btn1.1, fx2_btn2.1, fx2_btn3.1, fx2_btn4.1, fx2_enc1.1, fx2_enc2.1, fx2_enc3.1, fxEncBtns1.16, pfl_btn_1.1, pfl_btn_2.1, pfl_btn_3.1, pfl_btn_4.1, pfl_btn_master1.1, spare28.1, spare29.1, vu_matrix.1
GND: 3.3V_In.2, C1.2, C2.2, C3.1, C4.1, C5.1, C6.1, C7.1, C8.1, C9.1, C10.1, C11.1, C12.1, FX-BTNs1.6, FX-BTNs1.7, FX-BTNs1.8, MuxCh1.6, MuxCh1.7, MuxCh1.8, MuxCh1_1.3, MuxCh1_2.3, MuxCh1_3.3, MuxCh1_4.3, MuxCh1_5.3, MuxCh1_6.3, MuxCh1_7.3, MuxCh1_8.3, MuxCh2.6, MuxCh2.7, MuxCh2.8, MuxCh2_1.3, MuxCh2_2.3, MuxCh2_3.3, MuxCh2_4.3, MuxCh2_5.3, MuxCh2_6.3, MuxCh2_7.3, MuxCh2_8.3, MuxCh3.6, MuxCh3.7, MuxCh3.8, MuxCh3_1.3, MuxCh3_2.3, MuxCh3_3.3, MuxCh3_4.3, MuxCh3_5.3, MuxCh3_6.3, MuxCh3_7.3, MuxCh3_8.3, MuxCh4.6, MuxCh4.7, MuxCh4.8, MuxCh4_1.3, MuxCh4_2.3, MuxCh4_3.3, MuxCh4_4.3, MuxCh4_5.3, MuxCh4_6.3, MuxCh4_7.3, MuxCh4_8.3, MuxCh5.6, MuxCh5.7, MuxCh5.8, MuxCh5_1.3, MuxCh5_2.3, MuxCh5_3.3, MuxCh5_4.3, MuxCh5_5.3, MuxCh5_6.3, MuxCh5_7.3, MuxCh5_8.3, NeoPixel1.3, R1.2, R2.2, R3.2, R4.2, R5.2, R6.2, R7.2, R8.2, R9.2, R10.2, R11.2, R12.2, R13.2, R14.2, R15.2, R16.2, R17.2, R19.2, R20.2, R21.2, R22.2, R23.2, R24.2, R25.2, R26.2, R27.2, R28.2, R29.2, R34.2, R35.2, R36.2, R37.2, R38.2, R39.2, R40.2, R41.2, R42.2, R43.2, R44.2, R45.2, R46.2, R47.2, R48.2, R49.2, R50.2, R51.2, R52.2, R53.2, R54.2, R55.2, R56.2, R57.2, R58.2, R59.2, R60.2, R61.2, R62.2, R63.2, R64.2, R65.2, R66.2, R67.2, U5.1, U5.34, U5.47, display_1.2, display_2.2, fx1_enc1.2, fx1_enc2.2, fx1_enc3.2, fx2_enc1.2, fx2_enc2.2, fx2_enc3.2, fxEncBtns1.6, fxEncBtns1.7, fxEncBtns1.8, pfl_led_1.2, pfl_led_2.2, pfl_led_3.2, pfl_led_4.2, pfl_led_master1.2, spare28.3, spare29.3, vu_matrix.2
unnamed: 3.3V_Test1.1, C3.2, U5.15
unnamed: 3.3V_Test2.1, U5.46
unnamed: FX-BTNs1.1, R5.1, fx2_btn1.2
unnamed: FX-BTNs1.2, R7.1, fx2_btn3.2
unnamed: FX-BTNs1.4, R8.1, fx2_btn4.2
unnamed: FX-BTNs1.5, R6.1, fx2_btn2.2
unnamed: FX-BTNs1.12, R4.1, fx1_btn4.2
unnamed: FX-BTNs1.13, R1.1, fx1_btn1.2
unnamed: FX-BTNs1.14, R2.1, fx1_btn2.2
unnamed: FX-BTNs1.15, R3.1, fx1_btn3.2
unnamed: MuxCh1.1, MuxCh1_5.2, R13.1
unnamed: MuxCh1.2, MuxCh1_7.2, R15.1
unnamed: MuxCh1.4, MuxCh1_8.2, R16.1
unnamed: MuxCh1.5, MuxCh1_6.2, R14.1
unnamed: MuxCh1.12, MuxCh1_4.2, R12.1
unnamed: MuxCh1.13, MuxCh1_1.2, R9.1
unnamed: MuxCh1.14, MuxCh1_2.2, R10.1
unnamed: MuxCh1.15, MuxCh1_3.2, R11.1
unnamed: MuxCh2.13, MuxCh2_1.2, R22.1
unnamed: MuxCh2.14, MuxCh2_2.2, R23.1
unnamed: MuxCh2.15, MuxCh2_3.2, R24.1
unnamed: MuxCh2.12, MuxCh2_4.2, R25.1
unnamed: MuxCh2.1, MuxCh2_5.2, R26.1
unnamed: MuxCh2.5, MuxCh2_6.2, R27.1
unnamed: MuxCh2.2, MuxCh2_7.2, R28.1
unnamed: MuxCh2.4, MuxCh2_8.2, R29.1
unnamed: MuxCh3.13, MuxCh3_1.2, R44.1
unnamed: MuxCh3.14, MuxCh3_2.2, R45.1
unnamed: MuxCh3.15, MuxCh3_3.2, R46.1
unnamed: MuxCh3.12, MuxCh3_4.2, R47.1
unnamed: MuxCh3.1, MuxCh3_5.2, R48.1
unnamed: MuxCh3.5, MuxCh3_6.2, R49.1
unnamed: MuxCh3.2, MuxCh3_7.2, R50.1
unnamed: MuxCh3.4, MuxCh3_8.2, R51.1
unnamed: MuxCh4.13, MuxCh4_1.2, R52.1
unnamed: MuxCh4.14, MuxCh4_2.2, R53.1
unnamed: MuxCh4.15, MuxCh4_3.2, R54.1
unnamed: MuxCh4.12, MuxCh4_4.2, R55.1
unnamed: MuxCh4.1, MuxCh4_5.2, R56.1
unnamed: MuxCh4.5, MuxCh4_6.2, R57.1
unnamed: MuxCh4.2, MuxCh4_7.2, R58.1
unnamed: MuxCh4.4, MuxCh4_8.2, R59.1
unnamed: MuxCh5.13, MuxCh5_1.2, R60.1
unnamed: MuxCh5.14, MuxCh5_2.2, R61.1
unnamed: MuxCh5.15, MuxCh5_3.2, R62.1
unnamed: MuxCh5.12, MuxCh5_4.2, R63.1
unnamed: MuxCh5.1, MuxCh5_5.2, R64.1
unnamed: MuxCh5.5, MuxCh5_6.2, R65.1
unnamed: MuxCh5.2, MuxCh5_7.2, R66.1
unnamed: MuxCh5.4, MuxCh5_8.2, R67.1
unnamed: R18.1, U5.18
unnamed: R30.2, U5.33
unnamed: R31.2, U5.32
unnamed: R32.2, U5.31
unnamed: R33.2, U5.30
unnamed: fx1_enc1.3, fxEncBtns1.13
unnamed: fx1_enc2.3, fxEncBtns1.14
unnamed: fx1_enc3.3, fxEncBtns1.15
unnamed: fx2_enc1.3, fxEncBtns1.12
unnamed: fx2_enc2.3, fxEncBtns1.1
unnamed: fx2_enc3.3, fxEncBtns1.5
display_scl1: U5.38, display_1.4
display_scl2: U5.16, display_2.4
display_sda1: U5.39, display_1.3
display_sda2: U5.17, display_2.3
mux_ch1: MuxCh1.3, R38.1, U5.41
mux_ch2: MuxCh2.3, R37.1, U5.42
mux_ch3: MuxCh3.3, R36.1, U5.43
mux_ch4: MuxCh4.3, R35.1, U5.44
mux_encBtn_fx: R17.1, U5.14, fxEncBtns1.3
mux_master: MuxCh5.3, R34.1, U5.45
mux_selBtn_fx: FX-BTNs1.3, R19.1, U5.19
neopixel: NeoPixel1.2, U5.35
pfl_btn_ch1: R43.1, U5.25, pfl_btn_1.2
pfl_btn_ch2: R42.1, U5.26, pfl_btn_2.2
pfl_btn_ch3: R41.1, U5.27, pfl_btn_3.2
pfl_btn_ch4: R40.1, U5.28, pfl_btn_4.2
pfl_btn_master: R39.1, U5.29, pfl_btn_master1.2
pfl_led_ch1: R18.2, pfl_led_1.1
pfl_led_ch2: R33.1, pfl_led_2.1
pfl_led_ch3: R32.1, pfl_led_3.1
pfl_led_ch4: R31.1, pfl_led_4.1
pfl_led_master: R30.1, pfl_led_master1.1
pin28: R20.1, U5.20, spare28.2
pin29: R21.1, U5.21, spare29.2
rEnc0_DT: U5.2, fx1_enc1.4
rEnc0_clk: U5.3, fx1_enc1.5
rEnc1_DT: U5.4, fx1_enc2.4
rEnc1_clk: U5.5, fx1_enc2.5
rEnc2_DT: U5.6, fx1_enc3.4
rEnc2_clk: U5.7, fx1_enc3.5
rEnc3_DT: U5.8, fx2_enc1.4
rEnc3_clk: U5.9, fx2_enc1.5
rEnc4_DT: U5.10, fx2_enc2.4
rEnc4_clk: U5.11, fx2_enc2.5
rEnc5_DT: U5.12, fx2_enc3.4
rEnc5_clk: U5.13, fx2_enc3.5
s0: FX-BTNs1.11, MuxCh1.11, MuxCh2.11, MuxCh3.11, MuxCh4.11, MuxCh5.11, U5.22, fxEncBtns1.11
s1: FX-BTNs1.10, MuxCh1.10, MuxCh2.10, MuxCh3.10, MuxCh4.10, MuxCh5.10, U5.23, fxEncBtns1.10
s2: FX-BTNs1.9, MuxCh1.9, MuxCh2.9, MuxCh3.9, MuxCh4.9, MuxCh5.9, U5.24, fxEncBtns1.9
vu_clk: U5.36, vu_matrix.5
vu_cs: U5.37, vu_matrix.4
vu_din: U5.40, vu_matrix.3

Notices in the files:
a3motion/v03/Poti-pcb/Poti-pcb.kicad_sch:
Licensed under CERN-OHL-S v2 or later
